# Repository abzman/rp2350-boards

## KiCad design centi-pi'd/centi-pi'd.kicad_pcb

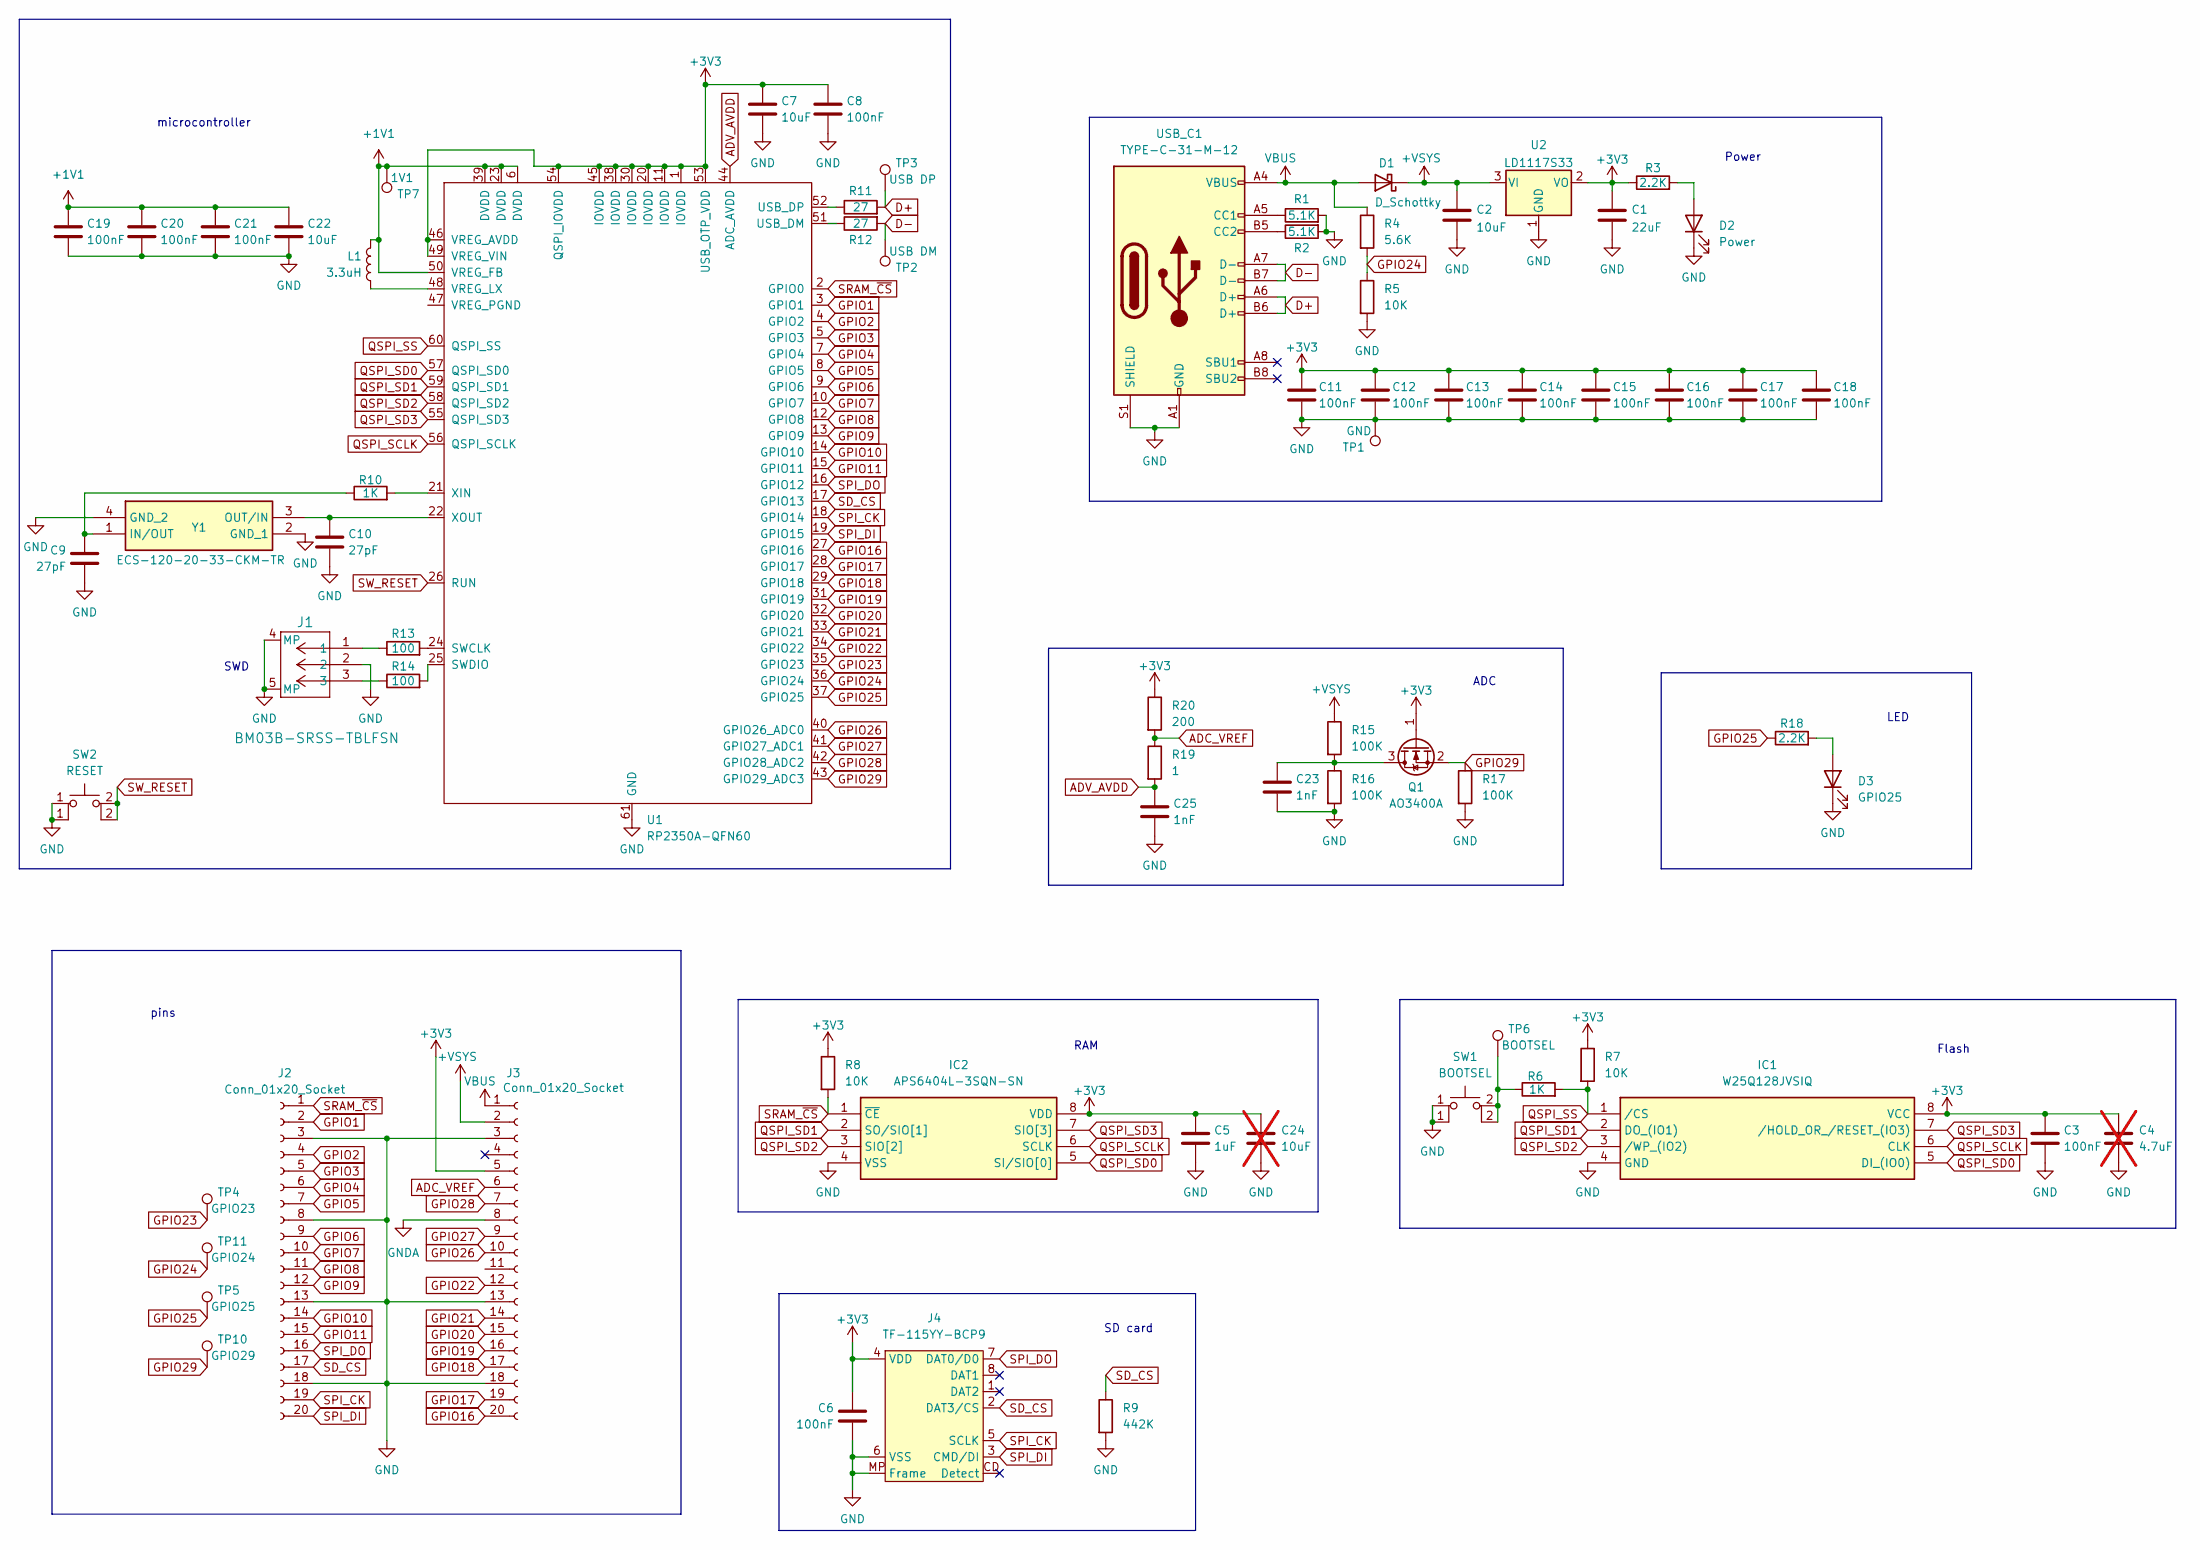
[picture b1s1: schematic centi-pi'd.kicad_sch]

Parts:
C1: 22uF; C_0603_1608Metric
C2, C7, C22: 10uF; C_0603_1608Metric
C3, C6, C8, C11, C12, C13, C14, C15, C16, C17, C18, C19, C20, C21: 100nF; C_0603_1608Metric
C4: 4.7uF; C_0603_1608Metric; not fitted
C5: 1uF; C_0603_1608Metric
C9, C10: 27pF; C_0603_1608Metric
C23, C25: 1nF; C_0603_1608Metric
C24: 10uF; C_0603_1608Metric; not fitted
D1: D_Schottky; D_SMA
D2: Power; LED_0603_1608Metric
D3: GPIO25; LED_0603_1608Metric
IC1: W25Q128JVSIQ; SOIC127P790X216-8N; Mouser Part Number 454-W25Q128JVSIQ
IC2: APS6404L-3SQN-SN; SOIC127P600X175-8N; Mouser Part Number 878-APS6404L-3SQN-SN
J1: BM03B-SRSS-TBLFSN; CONN_BM03B-SRSS-TBLFSN_JST
J2, J3: Conn_01x20_Socket; PinHeader_1x20_P2.54mm_Vertical
J4: TF-115YY-BCP9; TF-115YY-ACP9
L1: 3.3uH; L_1008_2520Metric
Q1: AO3400A; SOT-23
R1, R2: 5.1K; R_0603_1608Metric
R3, R18: 2.2K; R_0603_1608Metric
R4: 5.6K; R_0603_1608Metric
R5, R7, R8: 10K; R_0603_1608Metric
R6, R10: 1K; R_0603_1608Metric
R9: 442K; R_0603_1608Metric
R11, R12: 27; R_0603_1608Metric
R13, R14: 100; R_0603_1608Metric
R15, R16, R17: 100K; R_0603_1608Metric
R19: 1; R_0603_1608Metric
R20: 200; R_0603_1608Metric
SW1: BOOTSEL; SW_TH_Tactile_Omron_B3F-10xx
SW2: RESET; SW_TH_Tactile_Omron_B3F-10xx
TP1: GND; TestPoint_Pad_1.5x1.5mm
TP2: USB DM; TestPoint_Pad_1.5x1.5mm
TP3: USB DP; TestPoint_Pad_1.5x1.5mm
TP4: GPIO23; TestPoint_Pad_1.5x1.5mm
TP5: GPIO25; TestPoint_Pad_1.5x1.5mm
TP6: BOOTSEL; TestPoint_Pad_1.5x1.5mm
TP7: 1V1; TestPoint_Pad_1.5x1.5mm
TP10: GPIO29; TestPoint_Pad_1.5x1.5mm
TP11: GPIO24; TestPoint_Pad_1.5x1.5mm
U1: RP2350A-QFN60; RP2350A_QFN-60_EP_7.75x7.75_Pitch0.4mm
U2: LD1117S33; SOT-223-3_TabPin2
USB_C1: TYPE-C-31-M-12; USB_C_Receptacle_HRO_TYPE-C-31-M-12; LCSC C165948
Y1: ECS-120-20-33-CKM-TR; ECS1202033CKMTR; Mouser Part Number 520-120-20-33-CKMT

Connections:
+1V1: C19.1, C20.1, C21.1, C22.1, L1.1, TP7.1, U1.6 (DVDD), U1.23 (DVDD), U1.39 (DVDD), U1.50 (VREG_FB)
+3V3: C1.1, C3.1, C4.1, C5.1, C6.1, C7.1, C8.1, C11.1, C12.1, C13.1, C14.1, C15.1, C16.1, C17.1, C18.1, C24.1, IC1.8 (VCC), IC2.8 (VDD), J3.5, J4.4 (VDD), Q1.1 (G), R3.1, R7.1, R8.1, R20.1, U1.1 (IOVDD), U1.11 (IOVDD), U1.20 (IOVDD), U1.30 (IOVDD), U1.38 (IOVDD), U1.45 (IOVDD), U1.46 (VREG_AVDD), U1.49 (VREG_VIN), U1.53 (USB_OTP_VDD), U1.54 (QSPI_IOVDD), U2.2 (VO)
+VSYS: C2.1, D1.1 (K), J3.2, R15.1, U2.3 (VI)
ADC_VREF: J3.6, R19.1, R20.2
ADV_AVDD: C25.1, R19.2, U1.44 (ADC_AVDD)
D+: R11.2, TP3.1, USB_C1.A6 (D+), USB_C1.B6 (D+)
D-: R12.2, TP2.1, USB_C1.A7 (D-), USB_C1.B7 (D-)
GND: C1.2, C2.2, C3.2, C4.2, C5.2, C6.2, C7.2, C8.2, C9.2, C10.2, C11.2, C12.2, C13.2, C14.2, C15.2, C16.2, C17.2, C18.2, C19.2, C20.2, C21.2, C22.2, C23.2, C24.2, C25.2, D2.1 (K), D3.1 (K), IC1.4 (GND), IC2.4 (VSS), J1.2, J1.4 (MP), J1.5 (MP), J2.3, J2.8, J2.13, J2.18, J3.3, J3.13, J3.18, J4.6 (VSS), J4.MP (Frame), R1.2, R2.2, R5.2, R9.2, R16.2, R17.2, SW1.1, SW2.1, TP1.1, U1.61 (GND), U2.1 (GND), USB_C1.A1 (GND), USB_C1.A12 (GND), USB_C1.B1 (GND), USB_C1.B12 (GND), USB_C1.S1 (SHIELD), Y1.2 (GND_1), Y1.4 (GND_2)
GNDA: J3.8
GPIO1: J2.2, U1.3 (GPIO1)
GPIO2: J2.4, U1.4 (GPIO2)
GPIO3: J2.5, U1.5 (GPIO3)
GPIO4: J2.6, U1.7 (GPIO4)
GPIO5: J2.7, U1.8 (GPIO5)
GPIO6: J2.9, U1.9 (GPIO6)
GPIO7: J2.10, U1.10 (GPIO7)
GPIO8: J2.11, U1.12 (GPIO8)
GPIO9: J2.12, U1.13 (GPIO9)
GPIO10: J2.14, U1.14 (GPIO10)
GPIO11: J2.15, U1.15 (GPIO11)
GPIO16: J3.20, U1.27 (GPIO16)
GPIO17: J3.19, U1.28 (GPIO17)
GPIO18: J3.17, U1.29 (GPIO18)
GPIO19: J3.16, U1.31 (GPIO19)
GPIO20: J3.15, U1.32 (GPIO20)
GPIO21: J3.14, U1.33 (GPIO21)
GPIO22: J3.12, U1.34 (GPIO22)
GPIO23: TP4.1, U1.35 (GPIO23)
GPIO24: R4.2, R5.1, TP11.1, U1.36 (GPIO24)
GPIO25: R18.1, TP5.1, U1.37 (GPIO25)
GPIO26: J3.10, U1.40 (GPIO26_ADC0)
GPIO27: J3.9, U1.41 (GPIO27_ADC1)
GPIO28: J3.7, U1.42 (GPIO28_ADC2)
GPIO29: Q1.2 (S), R17.1, TP10.1, U1.43 (GPIO29_ADC3)
unnamed: D2.2 (A), R3.2
unnamed: D3.2 (A), R18.2
unnamed: J1.1, R13.1
unnamed: J1.3, R14.1
unnamed: C23.1, Q1.3 (D), R15.2, R16.1
unnamed: R6.1, SW1.2 (A), TP6.1
unnamed: R13.2, U1.24 (SWCLK)
unnamed: R14.2, U1.25 (SWDIO)
unnamed: R12.1, U1.51 (USB_DM)
unnamed: R11.1, U1.52 (USB_DP)
unnamed: L1.2, U1.48 (VREG_LX)
unnamed: R10.2, U1.21 (XIN)
unnamed: C10.1, U1.22 (XOUT), Y1.3 (OUT/IN)
unnamed: R1.1, USB_C1.A5 (CC1)
unnamed: R2.1, USB_C1.B5 (CC2)
unnamed: C9.1, R10.1, Y1.1 (IN/OUT)
QSPI_SCLK: IC1.6 (CLK), IC2.6 (SCLK), U1.56 (QSPI_SCLK)
QSPI_SD0: IC1.5 (DI_(IO0)), IC2.5 (SI/SIO[0]), U1.57 (QSPI_SD0)
QSPI_SD1: IC1.2 (DO_(IO1)), IC2.2 (SO/SIO[1]), U1.59 (QSPI_SD1)
QSPI_SD2: IC1.3 (/WP_(IO2)), IC2.3 (SIO[2]), U1.58 (QSPI_SD2)
QSPI_SD3: IC1.7 (/HOLD_OR_/RESET_(IO3)), IC2.7 (SIO[3]), U1.55 (QSPI_SD3)
QSPI_SS: IC1.1 (/CS), R6.2, R7.2, U1.60 (QSPI_SS)
SD_CS: J2.17, J4.2 (DAT3/CS), R9.1, U1.17 (GPIO13)
SPI_CK: J2.19, J4.5 (SCLK), U1.18 (GPIO14)
SPI_DI: J2.20, J4.3 (CMD/DI), U1.19 (GPIO15)
SPI_DO: J2.16, J4.7 (DAT0/D0), U1.16 (GPIO12)
SRAM_~CS: IC2.1 (~CE), J2.1, R8.2, U1.2 (GPIO0)
SW_RESET: SW2.2 (A), U1.26 (RUN)
VBUS: D1.2 (A), J3.1, R4.1, USB_C1.A4 (VBUS), USB_C1.A9 (VBUS), USB_C1.B4 (VBUS), USB_C1.B9 (VBUS)

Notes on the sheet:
Power
SWD
ADC
pins
SD card
RAM
microcontroller
Flash
LED

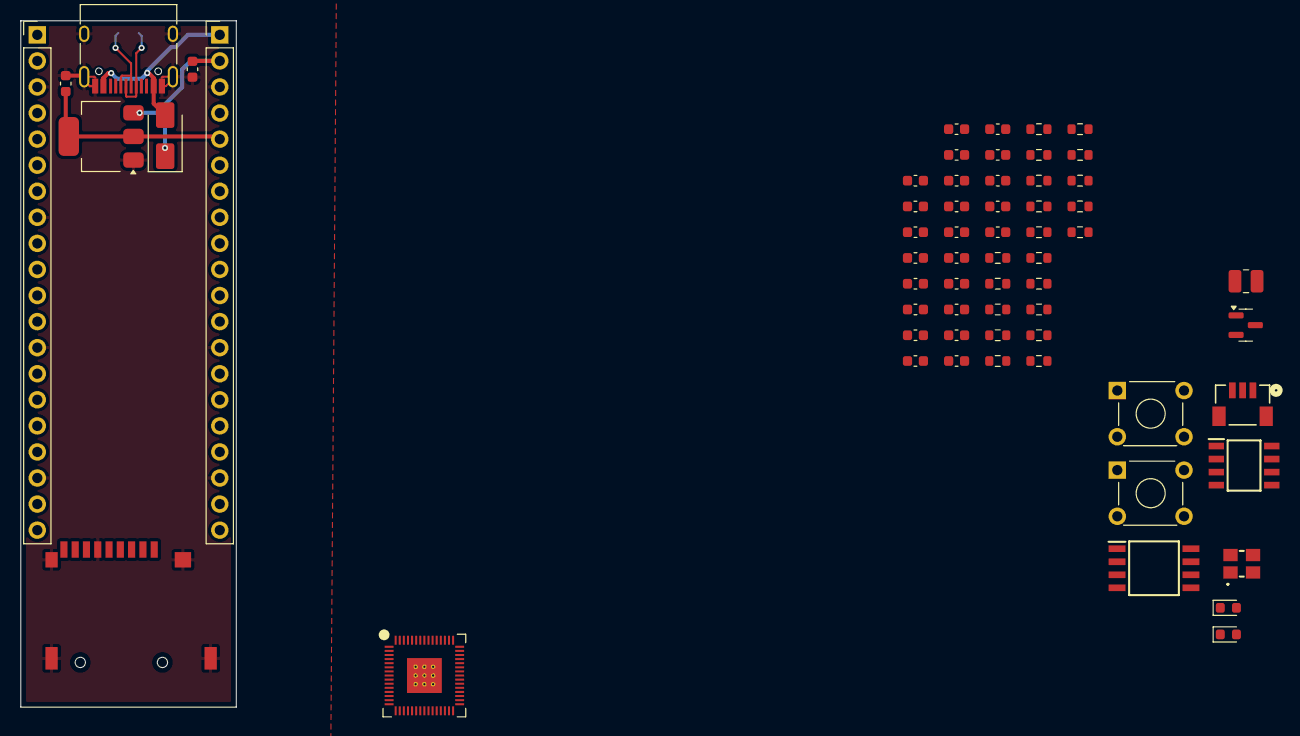
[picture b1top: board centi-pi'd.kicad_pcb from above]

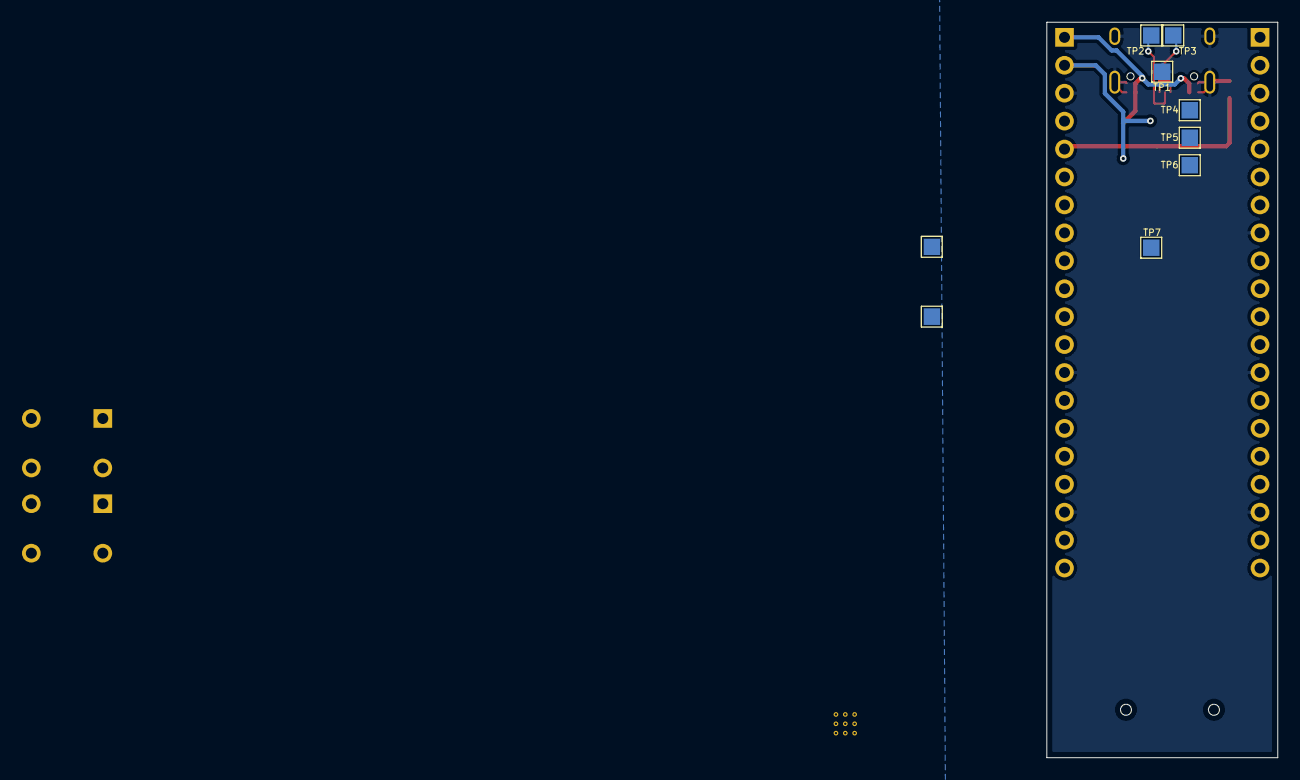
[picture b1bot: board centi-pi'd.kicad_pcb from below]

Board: 2 copper layers, 21.0 x 66.9 mm, 71 parts (9 on the bottom side), 62 nets.

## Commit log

2024-08-23 first pass schematic
2024-08-23 exported schematic as pdf
2024-08-23 first pass, long board
2024-08-27 started layout
